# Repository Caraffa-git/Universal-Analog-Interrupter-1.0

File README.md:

https://gitlab.com/universal-tc-interrupters

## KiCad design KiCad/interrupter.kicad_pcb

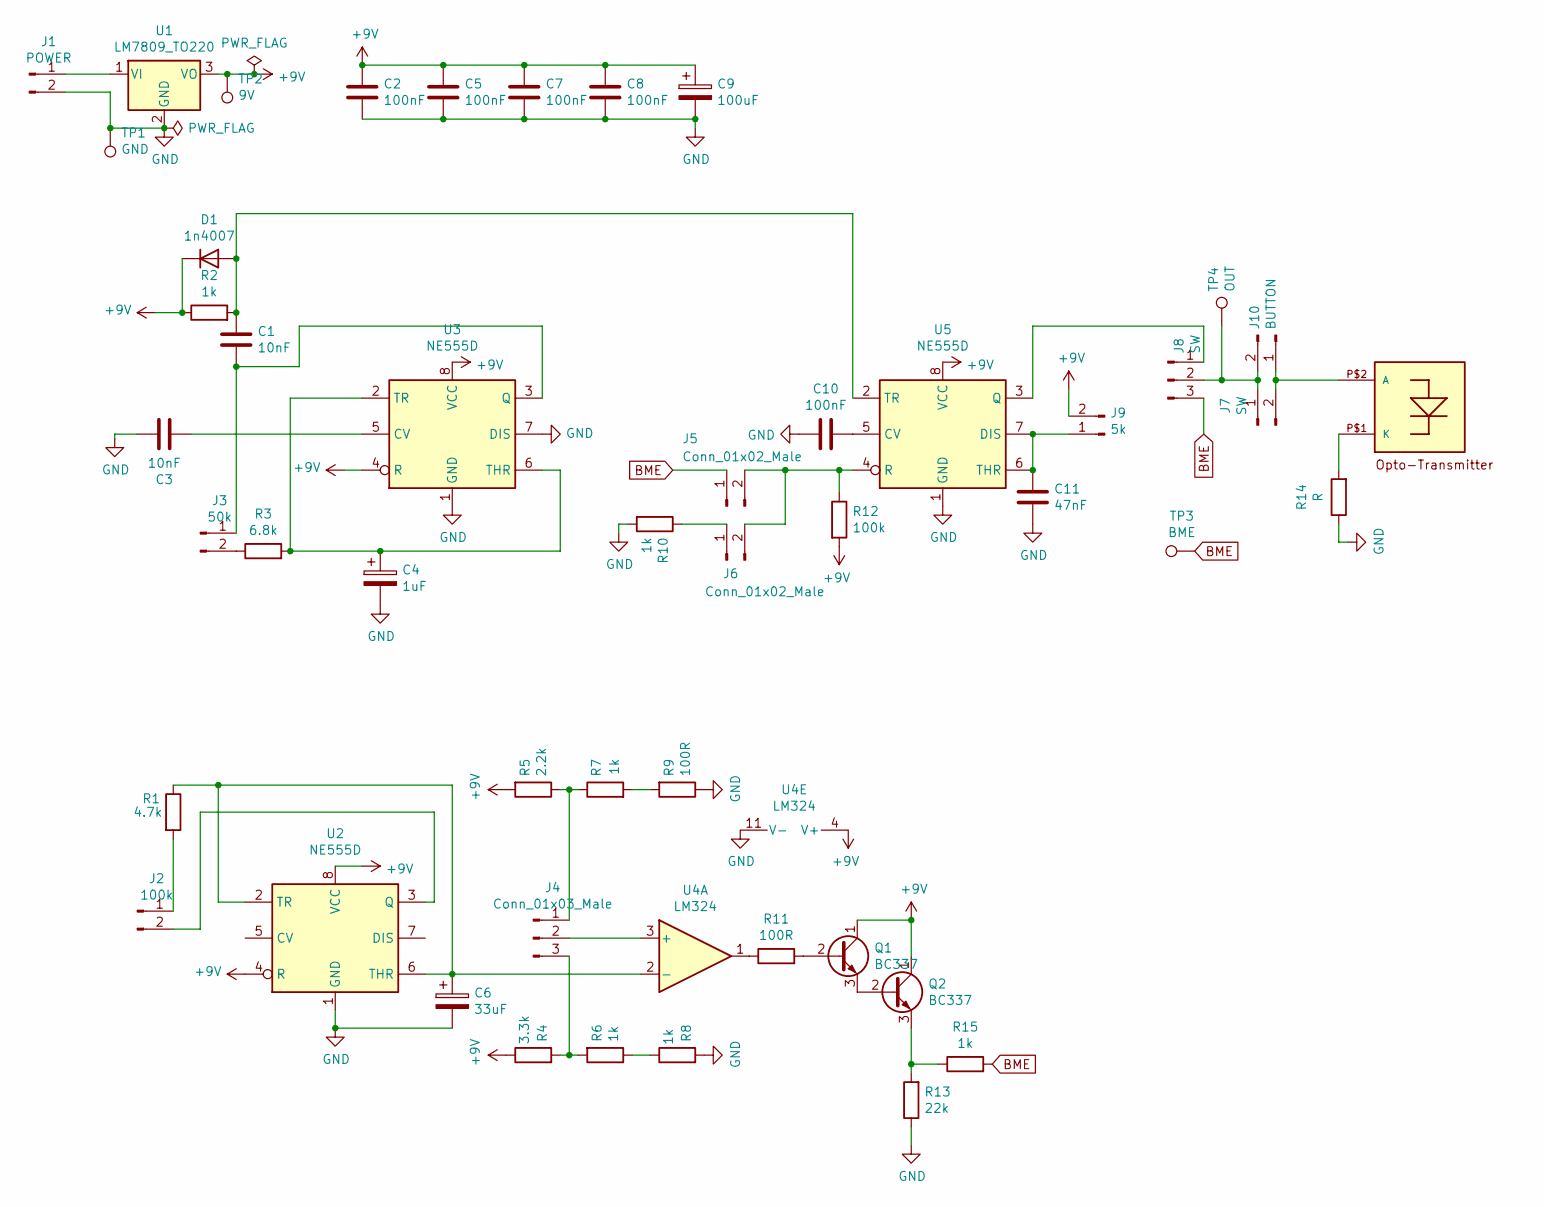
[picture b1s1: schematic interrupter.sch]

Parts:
C1, C3: 10nF; C_0805_2012Metric_Pad1.18x1.45mm_HandSolder
C2, C5, C7, C8, C10: 100nF; C_0805_2012Metric_Pad1.18x1.45mm_HandSolder
C4: 1uF; C_Radial_D4.0mm_H7.0mm_P1.50mm
C6: 33uF; C_Radial_D4.0mm_H7.0mm_P1.50mm
C9: 100uF; C_Radial_D8.0mm_H11.5mm_P3.50mm
C11: 47nF; C_0805_2012Metric_Pad1.18x1.45mm_HandSolder
D1: 1n4007; D_SMA_Handsoldering
J1: POWER; PinSocket_1x02_P2.54mm_Vertical
J2: 100k; PinSocket_1x02_P2.54mm_Vertical
J3: 50k; PinSocket_1x02_P2.54mm_Vertical
J4: Conn_01x03_Male; PinSocket_1x03_P2.54mm_Vertical
J5, J6: Conn_01x02_Male; PinSocket_1x02_P2.54mm_Vertical
J7: SW; PinSocket_1x02_P2.54mm_Vertical
J8: SW; PinSocket_1x03_P2.54mm_Vertical
J9: 5k; PinSocket_1x02_P2.54mm_Vertical
J10: BUTTON; PinSocket_1x02_P2.54mm_Vertical
Q1, Q2: BC337; TO-92_Inline
R1: 4.7k; R_0805_2012Metric_Pad1.20x1.40mm_HandSolder
R2, R6, R7, R8, R10, R15: 1k; R_0805_2012Metric_Pad1.20x1.40mm_HandSolder
R3: 6.8k; R_0805_2012Metric_Pad1.20x1.40mm_HandSolder
R4: 3.3k; R_0805_2012Metric_Pad1.20x1.40mm_HandSolder
R5: 2.2k; R_0805_2012Metric_Pad1.20x1.40mm_HandSolder
R9, R11: 100R; R_0805_2012Metric_Pad1.20x1.40mm_HandSolder
R12: 100k; R_0805_2012Metric_Pad1.20x1.40mm_HandSolder
R13: 22k; R_0805_2012Metric_Pad1.20x1.40mm_HandSolder
R14: R; R_Axial_DIN0207_L6.3mm_D2.5mm_P10.16mm_Horizontal
TP1: GND; TestPoint_Pad_1.5x1.5mm
TP2: 9V; TestPoint_Pad_1.5x1.5mm
TP3: BME; TestPoint_Pad_1.5x1.5mm
TP4: OUT; TestPoint_Pad_1.5x1.5mm
U1: LM7809_TO220; TO-220-3_Vertical
U2, U3, U5: NE555D; SOIC-8_3.9x4.9mm_P1.27mm
U4: LM324; SOIC-14_3.9x8.7mm_P1.27mm
U6: IFE91A; OPTO-TRANSMITTER

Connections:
+9V: C2.1, C5.1, C7.1, C8.1, C9.1, D1.1 (K), J9.2, Q1.1 (C), Q2.1 (C), R2.1, R4.1, R5.2, R12.2, TP2.1, U1.3 (VO), U2.4 (R), U2.8 (VCC), U3.4 (R), U3.8 (VCC), U4.4 (V+), U5.8 (VCC); also elsewhere on the board
BME: J5.1, J8.3, R15.2, TP3.1; also elsewhere on the board
GND: C2.2, C3.1, C4.2, C5.2, C6.2, C7.2, C8.2, C9.2, C10.2, C11.1, J1.2, R8.2, R9.1, R10.2, R13.1, R14.1, TP1.1, U1.2 (GND), U2.1 (GND), U3.1 (GND), U3.7 (DIS), U4.11 (V-), U5.1 (GND); also elsewhere on the board
unnamed: C1.1, D1.2 (A), R2.2, U5.2 (TR)
unnamed: C1.2, J3.1, U3.3 (Q)
unnamed: C3.2, U3.5 (CV)
unnamed: C4.1, R3.2, U3.2 (TR), U3.6 (THR)
unnamed: C6.1, R1.1, U2.2 (TR), U2.6 (THR), U4.2 (-)
unnamed: C10.1, U5.5 (CV)
unnamed: C11.2, J9.1, U5.6 (THR), U5.7 (DIS)
unnamed: J1.1, U1.1 (VI)
unnamed: J2.1, R1.2
unnamed: J2.2, U2.3 (Q)
unnamed: J3.2, R3.1
unnamed: J4.1, R5.1, R7.1
unnamed: J4.2, U4.3 (+)
unnamed: J4.3, R4.2, R6.2
unnamed: J5.2, J6.2, R12.1, U5.4 (R)
unnamed: J6.1, R10.1
unnamed: J8.1, U5.3 (Q)
unnamed: J7.2, J10.1, U6.P$2 (A)
unnamed 21: J7.1, J8.2, J10.2, TP4.1; also elsewhere on the board
unnamed: Q1.2 (B), R11.2
unnamed: Q1.3 (E), Q2.2 (B)
unnamed: Q2.3 (E), R13.2, R15.1
unnamed: R6.1, R8.1
unnamed: R7.2, R9.2
unnamed: R11.1, U4.1
unnamed: R14.2, U6.P$1 (K)

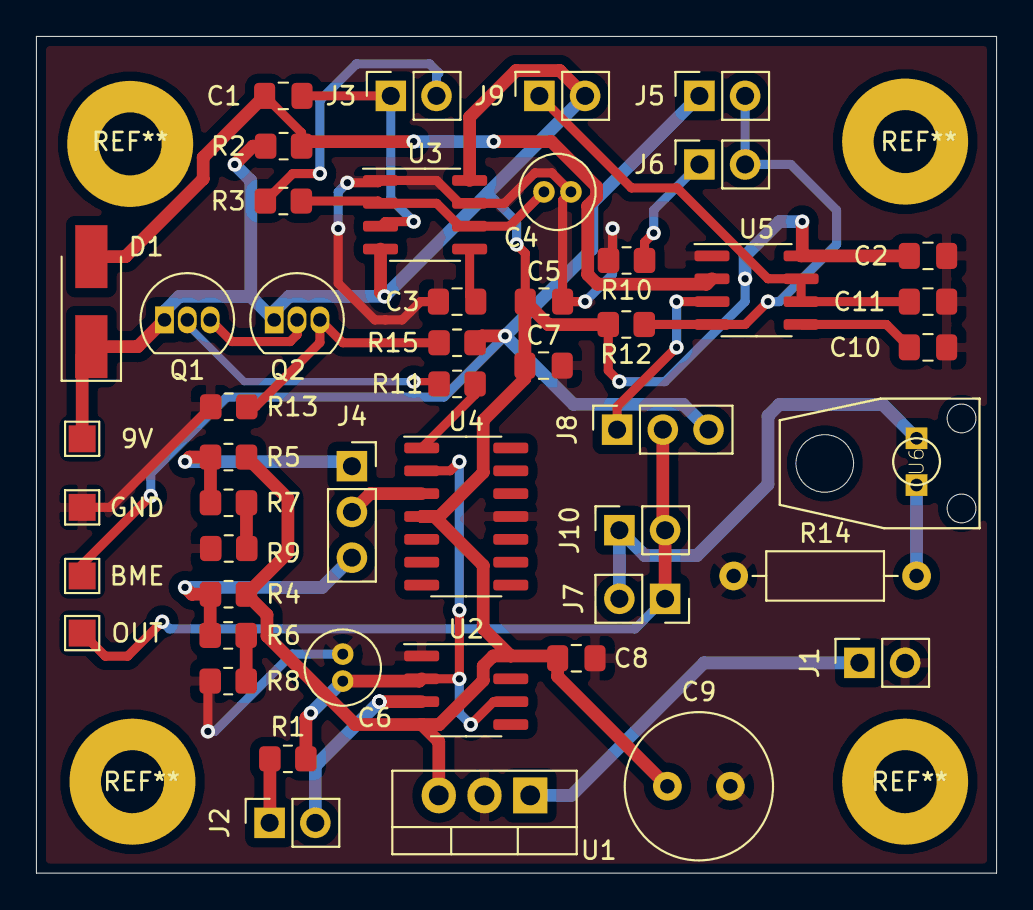
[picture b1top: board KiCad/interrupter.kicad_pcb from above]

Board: 2 copper layers, 53.3 x 46.5 mm, 49 parts (0 on the bottom side), 29 nets.

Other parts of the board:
9V: 9V; TestPoint_Pad_1.5x1.5mm
BME: BME; TestPoint_Pad_1.5x1.5mm
GND: GND; TestPoint_Pad_1.5x1.5mm
OUT: OUT; TestPoint_Pad_1.5x1.5mm

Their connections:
+9V: 9V.1; also elsewhere on the board
BME: BME.1; also elsewhere on the board
GND: GND.1; also elsewhere on the board
unnamed 21: OUT.1; also elsewhere on the board

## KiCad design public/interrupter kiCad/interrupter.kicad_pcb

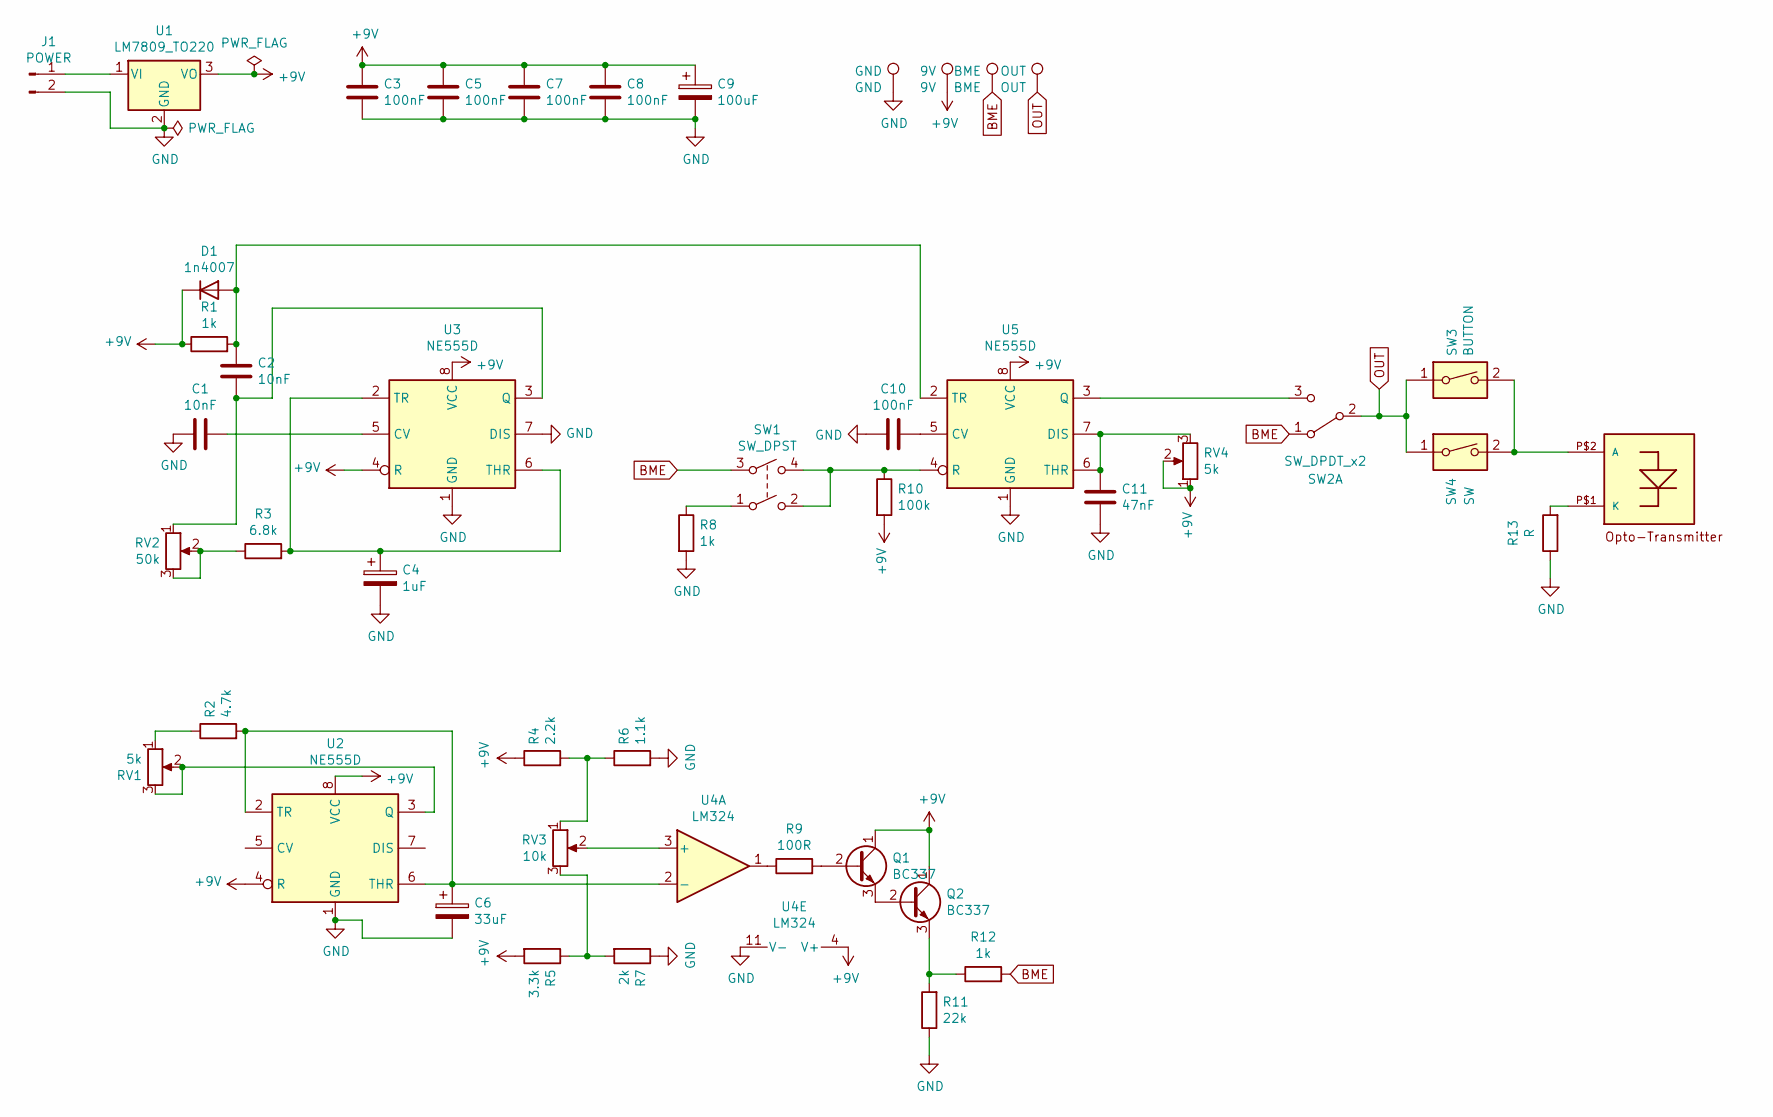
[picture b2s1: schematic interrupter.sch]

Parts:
9V: 9V; TestPoint_Pad_1.5x1.5mm
BME: BME; TestPoint_Pad_1.5x1.5mm
C1, C2: 10nF; C_0805_2012Metric_Pad1.18x1.45mm_HandSolder
C3, C5, C7, C8, C10: 100nF; C_0805_2012Metric_Pad1.18x1.45mm_HandSolder
C4: 1uF; C_Radial_D4.0mm_H7.0mm_P1.50mm
C6: 33uF; C_Radial_D4.0mm_H7.0mm_P1.50mm
C9: 100uF; C_Radial_D8.0mm_H11.5mm_P3.50mm
C11: 47nF; C_0805_2012Metric_Pad1.18x1.45mm_HandSolder
D1: 1n4007; D_SMA_Handsoldering
GND: GND; TestPoint_Pad_1.5x1.5mm
J1: POWER; PinSocket_1x02_P2.54mm_Vertical
OUT: OUT; TestPoint_Pad_1.5x1.5mm
Q1, Q2: BC337; TO-92_Inline
R1, R8, R12: 1k; R_0805_2012Metric_Pad1.20x1.40mm_HandSolder
R2: 4.7k; R_0805_2012Metric_Pad1.20x1.40mm_HandSolder
R3: 6.8k; R_0805_2012Metric_Pad1.20x1.40mm_HandSolder
R4: 2.2k; R_0805_2012Metric_Pad1.20x1.40mm_HandSolder
R5: 3.3k; R_0805_2012Metric_Pad1.20x1.40mm_HandSolder
R6: 1.1k; R_0805_2012Metric_Pad1.20x1.40mm_HandSolder
R7: 2k; R_0805_2012Metric_Pad1.20x1.40mm_HandSolder
R9: 100R; R_0805_2012Metric_Pad1.20x1.40mm_HandSolder
R10: 100k; R_0805_2012Metric_Pad1.20x1.40mm_HandSolder
R11: 22k; R_0805_2012Metric_Pad1.20x1.40mm_HandSolder
R13: R; R_Axial_DIN0207_L6.3mm_D2.5mm_P10.16mm_Horizontal
RV1, RV4: 5k; PinSocket_1x03_P2.54mm_Vertical
RV2: 50k; PinSocket_1x03_P2.54mm_Vertical
RV3: 10k; PinSocket_1x03_P2.54mm_Vertical
SW1: SW_DPST; PinSocket_2x02_P2.54mm_Vertical
SW2: SW_DPDT_x2; PinSocket_1x03_P2.54mm_Vertical
SW3: BUTTON; PinSocket_1x02_P2.54mm_Vertical
SW4: SW; PinSocket_1x02_P2.54mm_Vertical
U1: LM7809_TO220; TO-220-3_Vertical
U2, U3, U5: NE555D; SOIC-8_3.9x4.9mm_P1.27mm
U4: LM324; SOIC-14_3.9x8.7mm_P1.27mm
U6: IFE91A; OPTO-TRANSMITTER

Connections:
+9V: 9V.1, C3.1, C5.1, C7.1, C8.1, C9.1, D1.1 (K), Q1.1 (C), Q2.1 (C), R1.1, R4.1, R5.2, R10.2, RV4.1, RV4.2, U1.3 (VO), U2.4 (R), U2.8 (VCC), U3.4 (R), U3.8 (VCC), U4.4 (V+), U5.8 (VCC)
BME: BME.1, R12.2, SW1.3, SW2.1 (A)
GND: C1.2, C3.2, C4.2, C5.2, C6.2, C7.2, C8.2, C9.2, C10.2, C11.1, GND.1, J1.2, R6.2, R7.1, R8.2, R11.1, R13.1, U1.2 (GND), U2.1 (GND), U3.1 (GND), U3.7 (DIS), U4.11 (V-), U5.1 (GND)
unnamed: C1.1, U3.5 (CV)
unnamed: C2.1, D1.2 (A), R1.2, U5.2 (TR)
unnamed: C2.2, RV2.1, U3.3 (Q)
unnamed: C4.1, R3.2, U3.2 (TR), U3.6 (THR)
unnamed: C6.1, R2.2, U2.2 (TR), U2.6 (THR), U4.2 (-)
unnamed: C10.1, U5.5 (CV)
unnamed: C11.2, RV4.3, U5.6 (THR), U5.7 (DIS)
unnamed: J1.1, U1.1 (VI)
unnamed: Q1.2 (B), R9.2
unnamed: Q1.3 (E), Q2.2 (B)
unnamed: Q2.3 (E), R11.2, R12.1
unnamed: R2.1, RV1.1
unnamed: R3.1, RV2.2, RV2.3
unnamed: R4.2, R6.1, RV3.1
unnamed: R5.1, R7.2, RV3.3
unnamed: R8.1, SW1.1
unnamed: R9.1, U4.1
unnamed: R10.1, SW1.2, SW1.4, U5.4 (R)
unnamed: R13.2, U6.P$1 (K)
unnamed: RV1.2, RV1.3, U2.3 (Q)
unnamed: RV3.2, U4.3 (+)
unnamed: SW2.3 (C), U5.3 (Q)
unnamed: SW3.2, SW4.2, U6.P$2 (A)
OUT: OUT.1, SW2.2 (B), SW3.1, SW4.1

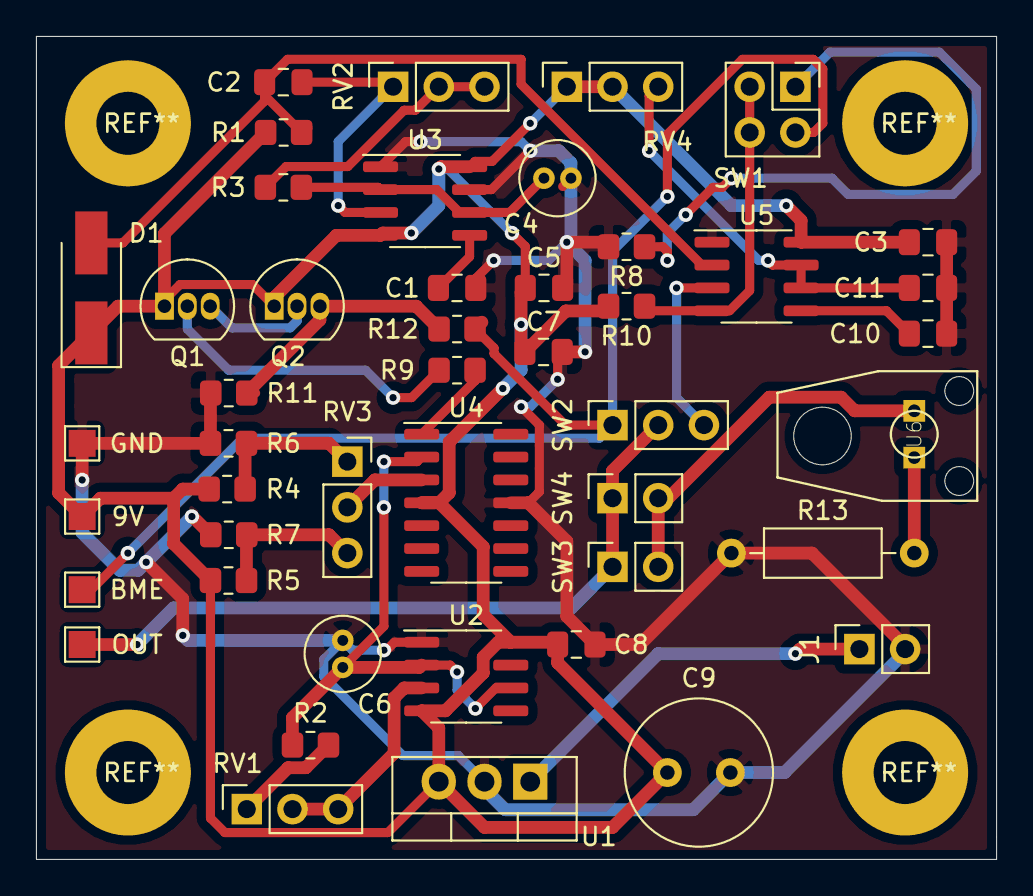
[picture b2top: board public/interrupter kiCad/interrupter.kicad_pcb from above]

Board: 2 copper layers, 53.3 x 45.7 mm, 46 parts (0 on the bottom side), 27 nets.
